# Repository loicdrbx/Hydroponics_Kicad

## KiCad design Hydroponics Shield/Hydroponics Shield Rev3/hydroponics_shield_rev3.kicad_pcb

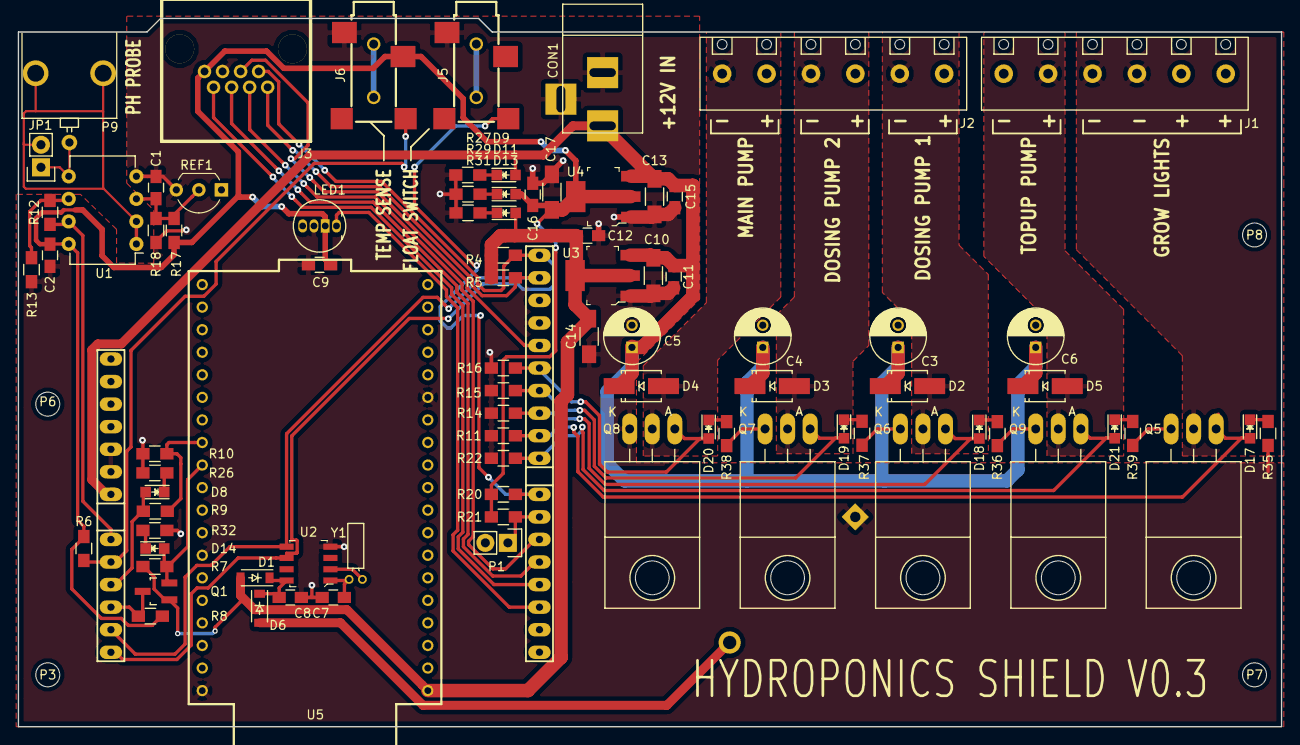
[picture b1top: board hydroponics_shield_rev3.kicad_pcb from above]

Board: 2 copper layers, 142.2 x 79.8 mm, 90 parts (1 on the bottom side), 47 nets.

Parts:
BAT1: BS-7_2032; BS-7_USER
C1, C2, C8, C9, C11, C12, C15, C16: 0.1uF; C_0805_HandSoldering
C3, C4, C5, C6: 5ZLH100MEFC6.3X11; C_Radial_D6.3_L11.2_P2.5
C7: 12.5pF NP0; C_0805_HandSoldering
C10, C13, C14, C17: 4.7uF; C_1206_HandSoldering
CON1: PJ-202A; BARREL_JACK
D1, D6: 1N4448W-TP; SOD-123
D2, D3, D4, D5: S1GTR; SMA_Handsoldering
D8, D9, D11, D13, D14, D17, D18, D19, D20, D21: GN; LED_0805
J1, J2: 282836-6
J3: RJHSE-5080
J5, J6: SJ-2523-SMT-TR
JP1: Jumper_NO_Small; Pin_Header_Straight_1x02
LED1: COM-12999(WS2812); LED-RGB-5MM_Common_Cathode
P1: CONN_01X02; Pin_Header_Straight_1x02
P3, P6, P7, P8: MTG; MountingHole_2-7mm
P9: 0731000105
Q1: DMN65D8L-7; SOT-23_Handsoldering
Q5, Q6, Q7, Q8, Q9: PSMN022-30PL,127; TO-220_Neutral123_Horizontal_LargePads
R4, R5: 2.0k; R_0805_HandSoldering
R6: 4.7k; R_0805_HandSoldering
R7, R8, R9, R10, R11, R14, R15, R16, R20, R21, R22: 10.0k; R_0805_HandSoldering
R12: 0; R_0805_HandSoldering
R13: DNP; R_0805_HandSoldering
R17, R18: 10.0k 0.1%; R_0805_HandSoldering
R26, R29, R35, R36, R37, R38, R39: 500; R_0805_HandSoldering
R27: 1.0k; R_0805_HandSoldering
R31, R32: 200; R_0805_HandSoldering
REF1: LT1004CZ-2.5; TO-92_Inline_Wide
SHIELD1: ARDUINO_SHIELD_R3_WI2C
U1: LMC6482IN; DIP-8_W7.62mm
U2: PCF8563; 8-SOIC
U3: AZ1117CH-3_3TRG1; SOT-223
U4: AZ1117CH-5TRG1; SOT-223
U5: ESP32_devkitc; ESP32_DEVKITC
Y1: CFS-20632768DZFB; Crystal_Round_Horizontal_2mm

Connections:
+3V3: C12.1, C14.1, D1.2, D13.2, Q1.1, R4.2, R5.2, R7.2, U3.2, U3.4, U5.3v3
+5V: C2.1, C9.2, C16.1, C17.1, D11.2, J3.1, J6.3, LED1.2, R6.2, R8.1, R17.1, R20.2, R21.2, U1.8, U4.2, U4.4
+12V: C3.1, C4.1, C5.1, C6.1, C10.1, C11.1, C13.1, C15.1, CON1.1, D2.1, D3.1, D4.1, D5.1, D9.2, J1.1, J1.2, J1.6, J2.1, J2.3, J2.5, SHIELD1.V_IN, U3.3, U4.3
/D1DRV: D2.2, J2.2, Q6.2
/D2DRV: D3.2, J2.4, Q7.2
/LEDDRV: J1.3, J1.4, Q5.2
/MPDRV: D4.2, J2.6, Q8.2
/TPDRV: D5.2, J1.5, Q9.2
AUX_BTTN1_IN: P1.1, R21.1, SHIELD1.6
BATT_BACKUP: BAT1.2, D6.2
DISPLAY_RESET: J3.5, SHIELD1.13
DOSING_PUMP_1: D18.2, Q6.1, R14.2, SHIELD1.10
DOSING_PUMP_2: D19.2, Q7.1, R15.2, SHIELD1.11
ENCODER_A: J3.2, SHIELD1.3
ENCODER_B: J3.4, SHIELD1.4
ENCODER_SW: J3.6, SHIELD1.5
FLOAT_SWITCH_IN: J5.2, R20.1, SHIELD1.7
GND: BAT1.1, C1.2, C2.2, C3.2, C4.2, C5.2, C6.2, C7.2, C8.1, C9.1, C10.2, C11.2, C12.2, C13.2, C14.2, C15.2, C16.2, C17.2, CON1.2, CON1.3, J3.3, J5.1, J6.1, LED1.3, P1.2, Q5.3, Q6.3, Q7.3, Q8.3, Q9.3, R10.1, R11.1, R13.1, R14.1, R15.1, R16.1, R18.2, R22.1, R26.2, R27.2, R29.2, R31.2, R32.2, R35.2, R36.2, R37.2, R38.2, R39.2, REF1.3, SHIELD1.GND1, SHIELD1.GND2, SHIELD1.GND3, U1.4, U2.4, U3.1, U4.1, U5.GND1, U5.GND2, U5.GND3
LED_STRIP_OUT: D17.2, Q5.1, R11.2, SHIELD1.9
MAIN_PUMP: D20.2, Q8.1, R16.2, SHIELD1.12
unnamed: C1.1, R17.2, R18.1, REF1.2, U1.3
unnamed: C7.1, U2.1, Y1.1
unnamed: C8.2, D1.1, D6.1, U2.8
unnamed: D8.1, R26.1
unnamed: D9.1, R27.1
unnamed: D11.1, R29.1
unnamed: D13.1, R31.1
unnamed: D14.1, R32.1
unnamed: D14.2, Q1.2, R7.1, U5.17
unnamed: D17.1, R35.1
unnamed: D18.1, R36.1
unnamed: D19.1, R37.1
unnamed: D20.1, R38.1
unnamed: D21.1, R39.1
unnamed: JP1.1, P9.1, U1.5
unnamed: R9.1, R10.2, U5.16
unnamed: R12.1, R13.2, U1.6
unnamed: U2.2, Y1.2
PH_VOUT: R12.2, SHIELD1.AD0, U1.7
RGB_OUT: LED1.1, SHIELD1.2
SCL: J3.7, R4.1, SHIELD1.AD5, SHIELD1.SCL, U2.6
SDA: J3.8, R5.1, SHIELD1.AD4, SHIELD1.SDA, U2.5
TEMP_SENSE_IN: J6.2, R6.1, SHIELD1.AD1
TOPUP_PUMP: D21.2, Q9.1, R22.2, SHIELD1.8
Vguard: JP1.2, P9.2, P9.3, U1.1, U1.2
WIFI_DATA_RECEIVE: Q1.3, R8.2, SHIELD1.AD3
WIFI_DATA_TRANSMIT: D8.2, R9.2, SHIELD1.AD2

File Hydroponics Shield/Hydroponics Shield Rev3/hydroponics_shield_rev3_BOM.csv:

,,,,,
,,,,,
,,,,,
,,,,,
,,,,,
,,,,,
,,,,,
,,,,,
,,,,,
,,,,,
,,,,,
,,,,,
,,,,,
,,,,,
Item,Refs,Qty,Value,PART NUMBER,
1,BAT1 ,1,BS-7_2032,HOLDER COINCELL 2032 RETAINRCLIP,
2,C1 C2 C8 C9 C11 C12 C15 C16 ,8,0.1uF,C2012X7R2A104K125AA,
3,C3 C4 C5 C6 ,4,5ZLH100MEFC6.3X11,5ZLH100MEFC6.3X11,
4,C7 ,1,12.5pF NP0,CL21C130JBANNNC,
5,C10 C13 C14 C17 ,4,4.7uF,GCM31CR71E475KA55K,
6,CON1 ,1,PJ-202A,PJ-202A,
7,D1 D6 ,2,1N4448W-TP,1N4448W-TP,
8,D2 D3 D4 D5 ,4,S1GTR,S1GTR,
9,D8 D9 D11 D13 D14 D17 D18 D19 D20 D21 ,10,GN,LTST-C171GKT,
10,J1 J2 ,2,282836-6,282836-6,
11,J3 ,1,RJHSE-5080,RJHSE-5080,
12,J5 J6 ,2,SJ-2523-SMT-TR,SJ-2523-SMT-TR,
13,JP1 ,1,Jumper_NO_Small,M20-9990246,
14,LED1 ,1,COM-12999(WS2812),COM-12999(WS2812),
15,P1 ,1,CONN_01X02,M20-9990246,
16,P3 P6 P7 P8 ,4,MTG,N/A,
17,P9 ,1,731000105,731000105,
18,Q1 ,1,DMN65D8L-7,DMN65D8L-7,
19,Q5 Q6 Q7 Q8 Q9 ,5,PSMN022-30PL,PSMN022-30PL, 
20,R4 R5 ,2,2.0k,ERJ-3EKF2001V,
21,R6 ,1,4.7k,RR1220P-472-D,
22,R7 R8 R9 R10 R11 R14 R15 R16 R20 R21 R22 ,11,10.0k,RR1220P-103-D,
23,R12 ,1,0,CRCW08050000Z0EA,
24,R13 ,1,DNP,N/A,
25,R17 R18 ,2,10.0k 0.1%,ERA-6AEB103V,
26,R26 R29 R35 R36 R37 R38 R39 ,7,500,ERJ-6ENF4990V,
27,R27 ,1,1.0k,ERJ-6ENF1001V,
28,R31 R32 ,2,200,RC0805FR-07200RL,
29,REF1 ,1,LT1004CZ-2.5,LT1004CZ-2.5,
30,SHIELD1 ,1,ARDUINO_SHIELD_R3_WI2C,N/A,
31,U1 ,1,LMC6482IN,LMC6482IN,
32,U2 ,1,PCF8563,"PCF8563T/5,518",
33,U3 ,1,AZ1117CH-3_3TRG1,IC REG LIN POS ADJ 800MA SOT223,
34,U4 ,1,AZ1117CH-5TRG1,IC REG LIN POS ADJ 800MA SOT223,
35,U5 ,1,ESP32_devkitc,ESP32-DEVKITC,
36,Y1 ,1,CFS-20632768DZFB,CFS-20632768DZFB,
,,,,,
,,,,,
,,,,,
,,,,,
,BOM made with KICAD_BOM_WIZARD (https://github.com/HashDefineElectronics/KiCad_BOM_Wizard.git),,,,
,Generated Mon 20 Aug 2018 02:13:16 PM EDT,,,,

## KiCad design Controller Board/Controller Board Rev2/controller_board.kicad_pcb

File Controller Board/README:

The controller board will ONLY work with 2.41" displays that use an SSD1305 controller IC, as this is the only one that can communicate via I2C
In addition, modifications must be made to the display for it to work. There is a set of jumpers on the back of the board, labelled BS1 and BS2

The jumpers must be set to the following positions:
BS1 - 1
BS2 - 0

This puts the display into I2C mode, and allows it to communicate with the shield

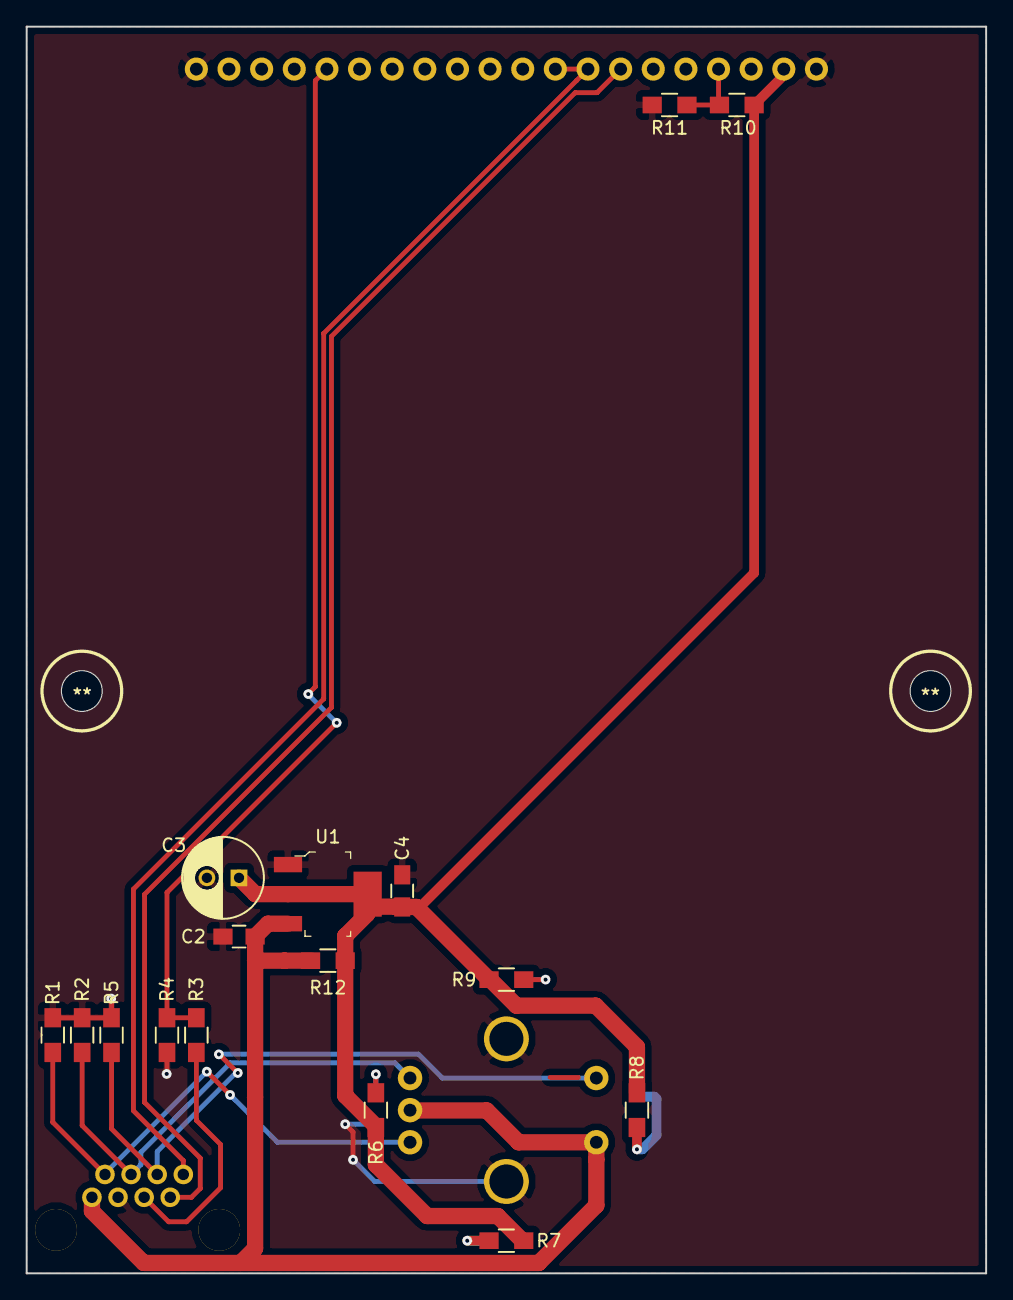
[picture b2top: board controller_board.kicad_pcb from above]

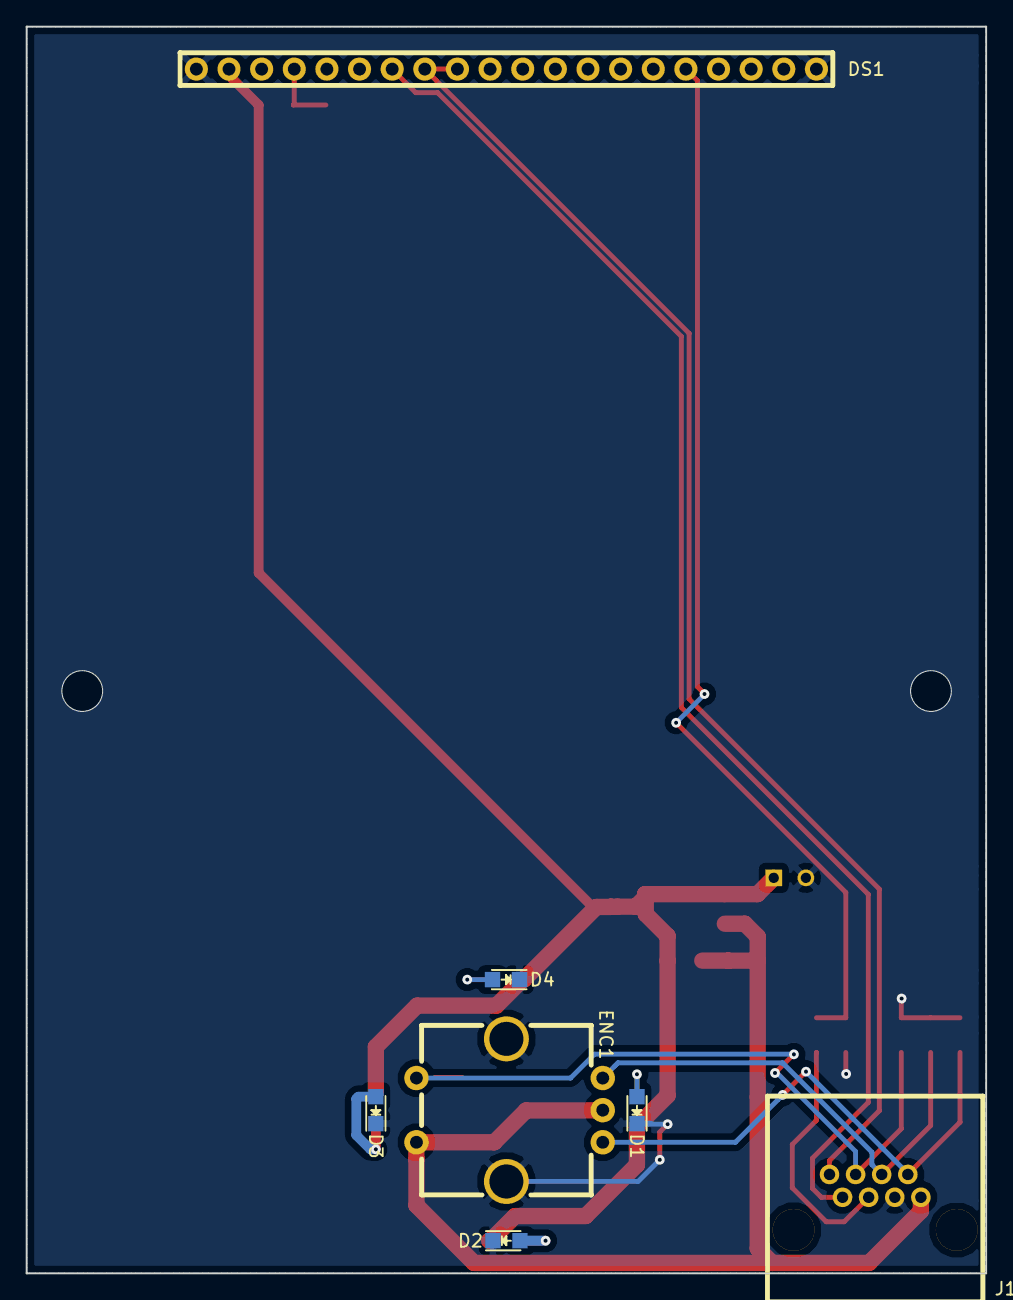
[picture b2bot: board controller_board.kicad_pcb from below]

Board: 2 copper layers, 74.7 x 97.0 mm, 25 parts (7 on the bottom side), 15 nets.

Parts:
**: MOUNTING_HOLE_0.125in
**#2: MOUNTING_HOLE_0.125in
C2, C4: 0.1uF; C_0805_HandSoldering
C3: 5ZLH100MEFC6.3X11; C_Radial_D6.3_L11.2_P2.5
D1, D2, D3, D4: GRN; LED_0805
DS1: OLED_GENERIC_SSD1305_20PIN_128x64; 128x64_OLED_20PIN_HORIZONTAL
ENC1: EC11K1524406
J1: RJHSE-5080
R1, R2, R3, R4, R5: 10.0k; R_0805_HandSoldering
R6, R7, R8, R9: 120; R_0805_HandSoldering
R10: 0; R_0805_HandSoldering
R11, R12: DNP; R_0805_HandSoldering
U1: AZ1117CH-3_3TRG1; SOT-223

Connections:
+3V3: C3.1, C4.1, DS1.2, R6.1, R7.1, R8.1, R9.1, R10.1, R12.1, U1.2, U1.4
ENCODER_A: ENC1.A, J1.2, R1.1
ENCODER_B: ENC1.B, J1.4, R2.1
ENCODER_SW: ENC1.E, J1.6, R5.1
GND: C2.2, C3.2, C4.2, D1.1, D2.1, D3.1, D4.1, DS1.1, DS1.20, ENC1.MTG1, ENC1.MTG2, J1.3, R1.2, R2.2, R4.2, R5.2, R11.2, U1.1
unnamed: D1.2, R6.2
unnamed: D2.2, R7.2
unnamed: D3.2, R8.2
unnamed: D4.2, R9.2
unnamed: DS1.4, R10.2, R11.1
unnamed: J1.5, R3.1
OLED_RESET: DS1.16, R3.2, R4.1
SCL: DS1.7, J1.7
SDA: DS1.8, DS1.9, J1.8
VCC: C2.1, ENC1.C, ENC1.D, J1.1, R12.2, U1.3

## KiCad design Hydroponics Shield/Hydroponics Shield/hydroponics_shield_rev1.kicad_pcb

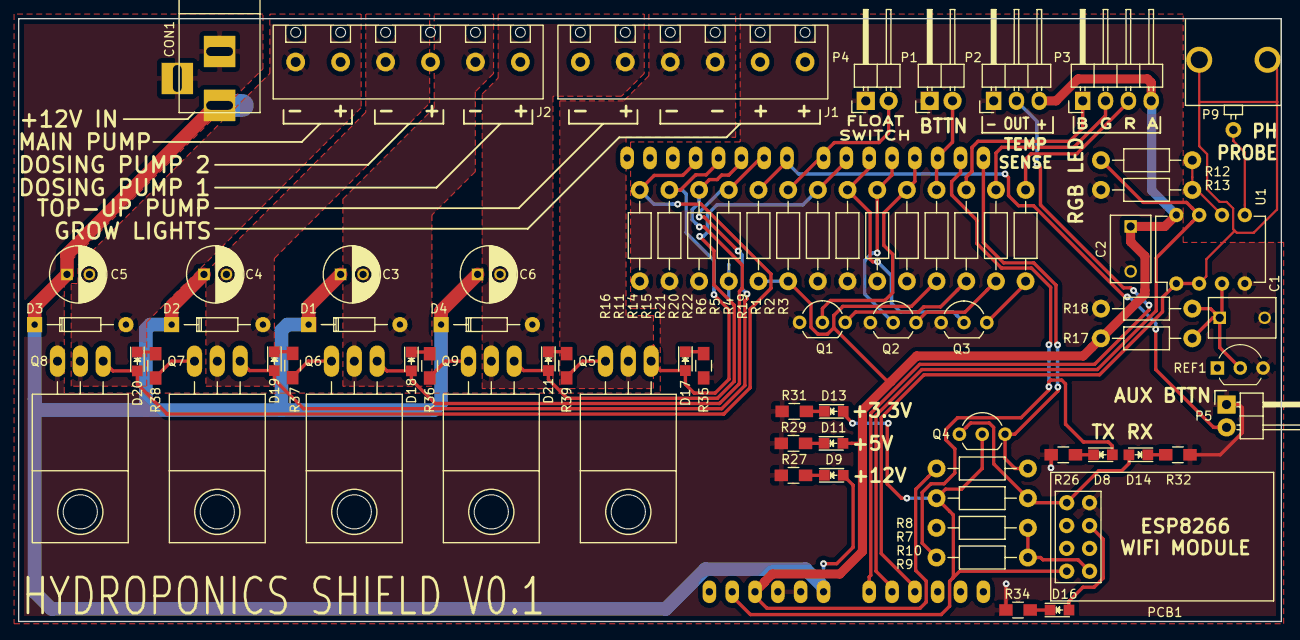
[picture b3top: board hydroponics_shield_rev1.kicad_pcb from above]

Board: 2 copper layers, 140.5 x 67.1 mm, 76 parts (0 on the bottom side), 48 nets.

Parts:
C1, C2: 0.1uF; C_Disc_D7.5_P5
C3, C4, C5, C6: 5ZLH100MEFC6.3X11; C_Radial_D6.3_L11.2_P2.5
CON1: PJ-202A; BARREL_JACK
D1, D2, D3, D4: 1N4148; Diode_DO-35_SOD27_Horizontal_RM10
D8, D9, D11, D13, D14, D16, D17, D18, D19, D20, D21: GN; LED_0805
J1, J2: 282836-6
P1, P4, P5: 22-05-3021; Pin_Header_Angled_1x02
P2: 0022053031; Pin_Header_Angled_1x03
P3: 0022053041; Pin_Header_Angled_1x04
P9: 0731000105
PCB1: ESP8266
Q1, Q2, Q3, Q4: 2N7000; TO-92_Inline_Wide
Q5, Q6, Q7, Q8, Q9: PSMN022-30PL,127; TO-220_Neutral123_Horizontal_LargePads
R1, R2, R3: R; Resistor_Horizontal_RM10mm
R4, R5, R6, R7, R8, R9, R10, R11, R12, R13, R14, R15, R16, R17, R18, R19, R20, R21, R22: 10.0k; Resistor_Horizontal_RM10mm
R26, R29, R35, R36, R37, R38, R39: 500; R_0805_HandSoldering
R27: 1.0k; R_0805_HandSoldering
R31, R32, R34: 200; R_0805_HandSoldering
REF1: LT1004CZ-2.5; TO-92_Inline_Wide
SHIELD1: ARDUINO_SHIELD; ARDUINO_SHIELD_NOSILK
U1: LMC6482IN; DIP-8_W7.62mm

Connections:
+3V3: D13.2, PCB1.8, Q4.2, R7.2, SHIELD1.3V3
+5V: C2.1, D11.2, P2.3, P3.4, R8.1, R17.1, R19.2, R20.2, R21.2, SHIELD1.5V, U1.8
+12V: C3.1, C4.1, C5.1, C6.1, CON1.1, D1.1, D2.1, D3.1, D4.1, D9.2, J1.1, J1.2, J1.6, J2.1, J2.3, J2.5, SHIELD1.V_IN
AUX_BTTN1_IN: P5.2, R21.1, SHIELD1.8
DOSING_PUMP_1: D18.2, Q6.1, R14.2, SHIELD1.10
DOSING_PUMP_2: D19.2, Q7.1, R15.2, SHIELD1.9
FLOAT_SWITCH_IN: P4.2, R20.1, SHIELD1.7
GND: C1.2, C2.2, CON1.2, CON1.3, P1.1, P2.1, P4.1, P5.1, PCB1.1, Q1.1, Q2.1, Q3.1, Q5.3, Q6.3, Q7.3, Q8.3, Q9.3, R4.1, R5.1, R6.1, R10.1, R11.1, R13.1, R14.1, R15.1, R16.1, R18.2, R22.1, R26.2, R27.2, R29.2, R31.2, R32.2, R34.2, R35.2, R36.2, R37.2, R38.2, R39.2, REF1.3, SHIELD1.GND1, SHIELD1.GND2, SHIELD1.GND3, U1.4
LED_B: Q3.2, R6.2, SHIELD1.5
LED_G: Q2.2, R5.2, SHIELD1.4
LED_R: Q1.2, R4.2, SHIELD1.3
LED_STRIP_OUT: D17.2, Q5.1, R11.2, SHIELD1.11
MAIN_PUMP: D20.2, Q8.1, R16.2, SHIELD1.12
unnamed: C1.1, R17.2, R18.1, REF1.2, U1.3
unnamed: C3.2, D1.2, J2.2, Q6.2
unnamed: C4.2, D2.2, J2.4, Q7.2
unnamed: C5.2, D3.2, J2.6, Q8.2
unnamed: C6.2, D4.2, J1.5, Q9.2
unnamed: D8.1, R26.1
unnamed: D9.1, R27.1
unnamed: D11.1, R29.1
unnamed: D13.1, R31.1
unnamed: D14.1, R32.1
unnamed: D14.2, PCB1.2, Q4.1, R7.1
unnamed: D16.1, R34.1
unnamed: D16.2, PCB1.3
unnamed: D17.1, R35.1
unnamed: D18.1, R36.1
unnamed: D19.1, R37.1
unnamed: D20.1, R38.1
unnamed: D21.1, R39.1
unnamed: J1.3, J1.4, Q5.2
unnamed: P3.1, R1.2
unnamed: P3.2, R2.2
unnamed: P3.3, R3.2
unnamed: P9.1, U1.5
unnamed: PCB1.7, R9.1, R10.2
unnamed: Q1.3, R1.1
unnamed: Q2.3, R2.1
unnamed: Q3.3, R3.1
unnamed: R12.1, R13.2, U1.6
PAIR_BTTN_IN: P1.2, R19.1, SHIELD1.2
PH_VOUT: R12.2, SHIELD1.AD1, U1.7
TEMP_SENSE_IN: P2.2, SHIELD1.AD0
TOPUP_PUMP: D21.2, Q9.1, R22.2, SHIELD1.6
Vguard: P9.2, P9.3, SHIELD1.AD2, U1.1, U1.2
WIFI_DATA_RECEIVE: Q4.3, R8.2, SHIELD1.0
WIFI_DATA_TRANSMIT: D8.2, R9.2, SHIELD1.1

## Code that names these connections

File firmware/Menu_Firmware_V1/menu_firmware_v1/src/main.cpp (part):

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#include <SoftwareSerial.h>

//pin definitions
#define DISPLAY_RESET 13
#define MAIN_PUMP_OUT 12
#define DOSING_PUMP_2 11
#define DOSING_PUMP_1 10
#define LED_STRIP_OUT 9
#define AUTO_TOPOFF_OUT 8
#define FLOAT_SWITCH_IN 7
#define AUX_BTTN_IN 6
#define ENCODER_SW_IN 5
#define ENCODER_B_IN 4
#define ENCODER_A_IN 3
#define RGB_LED_DOUT 2
#define TEMP_SENSE_IN A1
#define PH_IN A0
#define WIFI_TX A2
#define WIFI_RX A3
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void setupIO(void)
{
  pinMode(MAIN_PUMP_OUT,OUTPUT);
  pinMode(DOSING_PUMP_1,OUTPUT);
  pinMode(DOSING_PUMP_2,OUTPUT);
  pinMode(AUTO_TOPOFF_OUT,OUTPUT);
  pinMode(FLOAT_SWITCH_IN,INPUT);
}

char parseEncoderInput(void)
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
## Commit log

2018-05-04 desktop night changes
2018-05-04 workday additions
2018-05-08 changes made extra pump wifi
2018-05-09 finished board change from bt to wifi
2018-05-26 version 2 PCB redesign
2018-07-31 long overdue
2018-08-10 for Loic
2018-08-20 finished new rev3 board
2018-09-07 rev4
